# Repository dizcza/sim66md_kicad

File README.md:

# SIM66MD-R Kicad PCB

Designed in Kicad v8.0.

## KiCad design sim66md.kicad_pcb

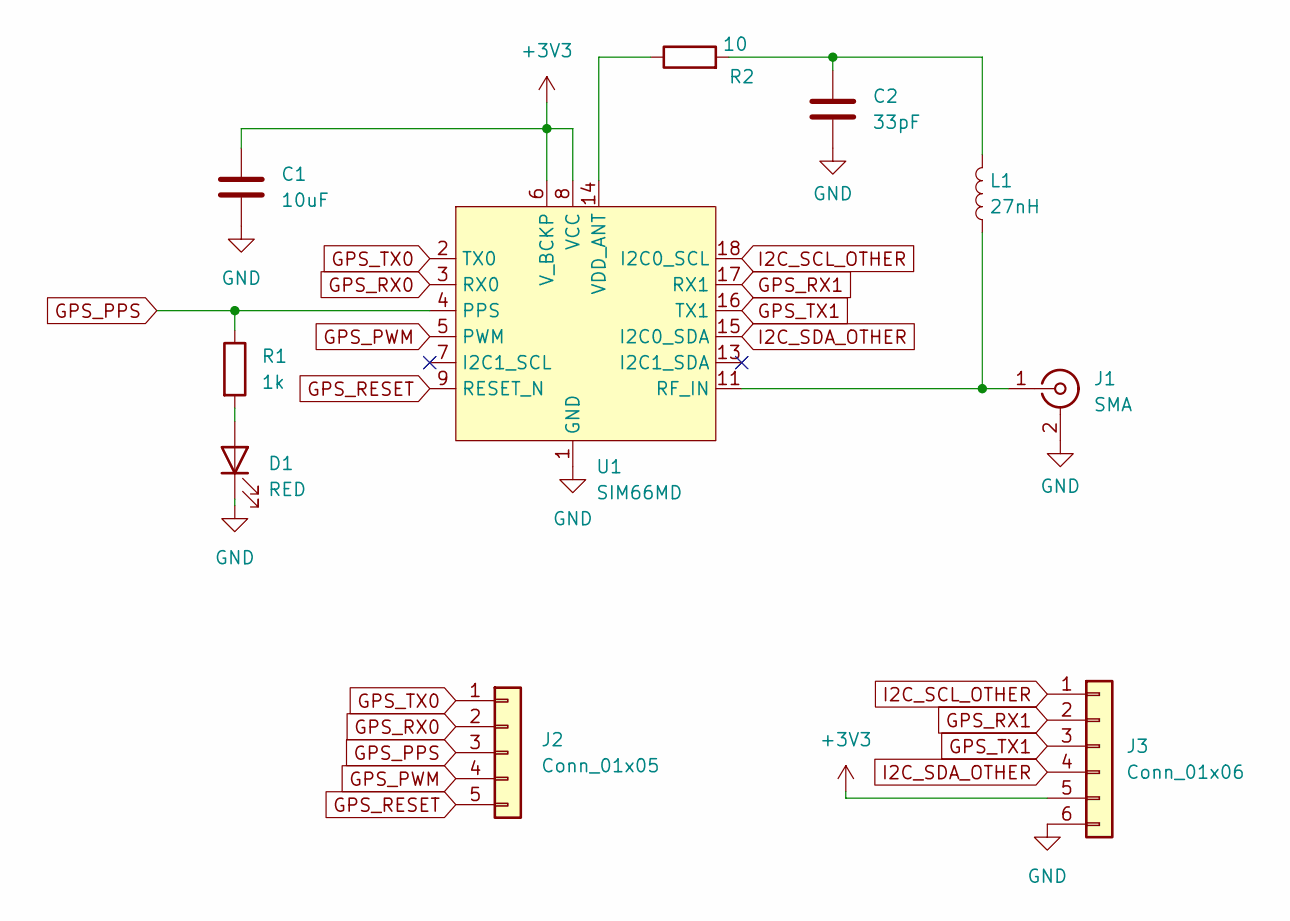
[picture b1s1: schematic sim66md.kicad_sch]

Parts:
C1: 10uF; C_0805_2012Metric_Pad1.18x1.45mm_HandSolder; LCSC C15850
C2: 33pF; C_0805_2012Metric_Pad1.18x1.45mm_HandSolder; LCSC C14857
D1: RED; LED_0603_1608Metric; LCSC C2286
J1: SMA; Conn_SMA_Amphenol_901-143_Horizontal_SmallerHoles
J2: Conn_01x05; PinSocket_1x05_P2.54mm_Vertical
J3: Conn_01x06; PinSocket_1x06_P2.54mm_Vertical
L1: 27nH; L_0805_2012Metric_Pad1.05x1.20mm_HandSolder; LCSC C98992
R1: 1k; R_0805_2012Metric_Pad1.20x1.40mm_HandSolder; LCSC C21190
R2: 10; R_0805_2012Metric_Pad1.20x1.40mm_HandSolder; LCSC C17415
U1: SIM66MD

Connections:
+3V3: C1.1, J3.5, U1.6 (V_BCKP), U1.8 (VCC)
GND: C1.2, C2.2, D1.1 (K), J1.2 (Ext), J3.6, U1.1 (GND), U1.10 (GND), U1.12 (GND)
GPS_PPS: J2.3, R1.1, U1.4 (PPS)
GPS_PWM: J2.4, U1.5 (PWM)
GPS_RESET: J2.5, U1.9 (RESET_N)
GPS_RX0: J2.2, U1.3 (RX0)
GPS_RX1: J3.2, U1.17 (RX1)
GPS_TX0: J2.1, U1.2 (TX0)
GPS_TX1: J3.3, U1.16 (TX1)
I2C_SCL_OTHER: J3.1, U1.18 (I2C0_SCL)
I2C_SDA_OTHER: J3.4, U1.15 (I2C0_SDA)
unnamed: C2.1, L1.2, R2.2
unnamed: D1.2 (A), R1.2
unnamed: J1.1 (In), L1.1, U1.11 (RF_IN)
unnamed: R2.1, U1.14 (VDD_ANT)

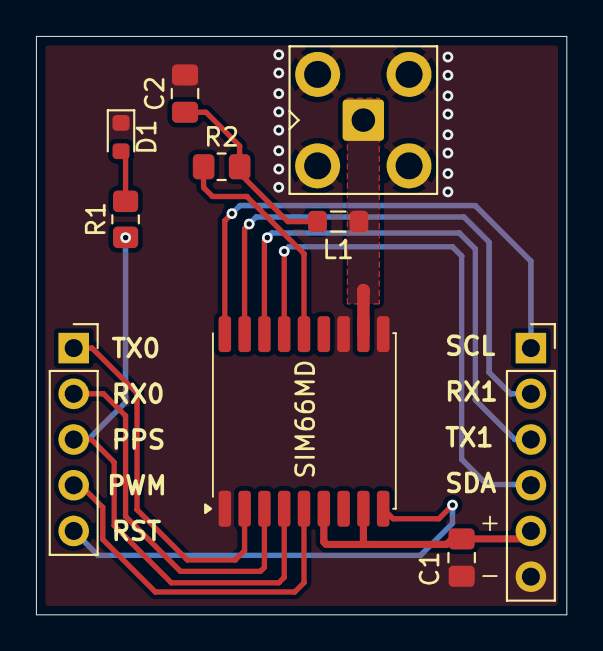
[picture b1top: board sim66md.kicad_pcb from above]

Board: 2 copper layers, 29.5 x 32.1 mm, 10 parts (0 on the bottom side), 15 nets.

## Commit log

2024-04-02 done
